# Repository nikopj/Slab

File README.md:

# Slab
Senior Lab: R3Cap, 3D RFID Motion Capture

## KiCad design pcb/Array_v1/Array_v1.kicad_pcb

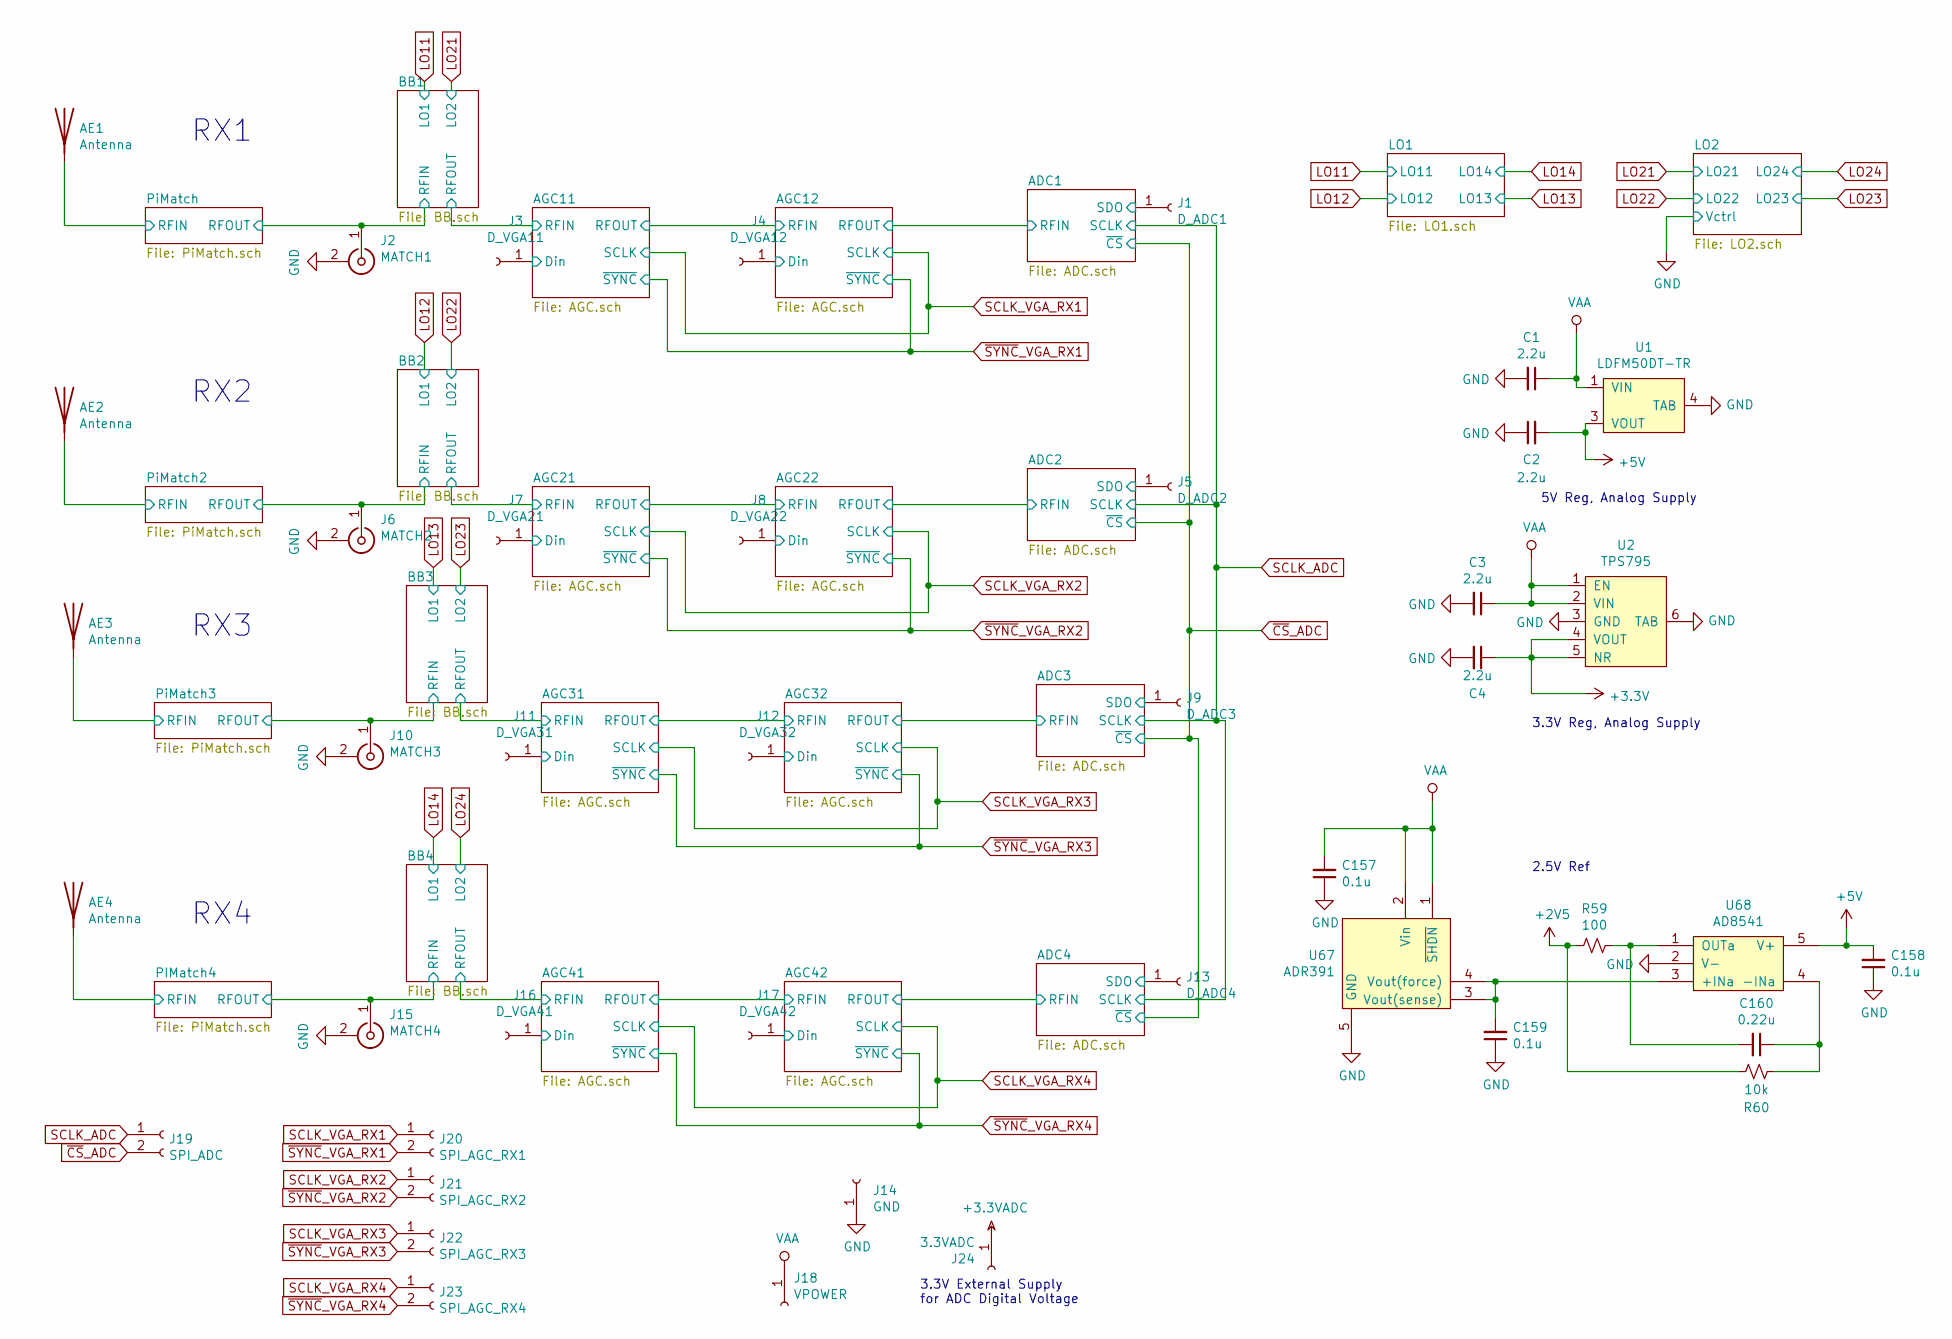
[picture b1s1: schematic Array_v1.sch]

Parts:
AE1, AE2, AE3, AE4: Antenna; 0915AT43A0026
C1, C2, C3, C4: 2.2u; C_0805_2012Metric
C157, C158, C159: 0.1u; C_0603_1608Metric
C160: 0.22u; C_0603_1608Metric
J1: D_ADC1; SolderWirePad_1x01_Drill0.8mm
J2: MATCH1; TE_5-1814832-1
J3: D_VGA11; SolderWirePad_1x01_Drill0.8mm
J4: D_VGA12; SolderWirePad_1x01_Drill0.8mm
J5: D_ADC2; SolderWirePad_1x01_Drill0.8mm
J6: MATCH2; TE_5-1814832-1
J7: D_VGA21; SolderWirePad_1x01_Drill0.8mm
J8: D_VGA22; SolderWirePad_1x01_Drill0.8mm
J9: D_ADC3; SolderWirePad_1x01_Drill0.8mm
J10: MATCH3; TE_5-1814832-1
J11: D_VGA31; SolderWirePad_1x01_Drill0.8mm
J12: D_VGA32; SolderWirePad_1x01_Drill0.8mm
J13: D_ADC4; SolderWirePad_1x01_Drill0.8mm
J14: GND; SolderWirePad_1x01_Drill0.8mm
J15: MATCH4; TE_5-1814832-1
J16: D_VGA41; SolderWirePad_1x01_Drill0.8mm
J17: D_VGA42; SolderWirePad_1x01_Drill0.8mm
J18: VPOWER; SolderWirePad_1x01_Drill0.8mm
J19: SPI_ADC; SolderWirePad_1x02_P3.81mm_Drill0.8mm
J20: SPI_AGC_RX1; SolderWirePad_1x02_P3.81mm_Drill0.8mm
J21: SPI_AGC_RX2; SolderWirePad_1x02_P3.81mm_Drill0.8mm
J22: SPI_AGC_RX3; SolderWirePad_1x02_P3.81mm_Drill0.8mm
J23: SPI_AGC_RX4; SON50P200X200X80-9N
J24: 3.3VADC; SolderWirePad_1x01_Drill0.8mm
R59: 100; C_0603_1608Metric
R60: 10k; C_0603_1608Metric
U1: LDFM50DT-TR; DPAK-TO252
U2: TPS795; SOT127P706X180-6N
U67: ADR391; SOT95P280X100-5N
U68: AD8541; SOT95P290X145-5N

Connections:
+2V5: R59.2, R60.2; also elsewhere on the board
+3.3VADC: J24.1; also elsewhere on the board
+3V3: C4.1, U2.4 (VOUT), U2.5 (NR); also elsewhere on the board
+5V: C2.2, C158.2, U1.3 (VOUT), U68.5 (V+); also elsewhere on the board
/ADC1/SDO: J1.1; also elsewhere on the board
/ADC2/SDO: J5.1; also elsewhere on the board
/ADC3/SDO: J9.1; also elsewhere on the board
/ADC4/SDO: J13.1; also elsewhere on the board
/AGC11/Din: J3.1; also elsewhere on the board
/AGC12/Din: J4.1; also elsewhere on the board
/AGC21/Din: J7.1; also elsewhere on the board
/AGC22/Din: J8.1; also elsewhere on the board
/AGC31/Din: J11.1; also elsewhere on the board
/AGC32/Din: J12.1; also elsewhere on the board
/AGC41/Din: J16.1; also elsewhere on the board
/AGC42/Din: J17.1; also elsewhere on the board
/BB1/RFIN: J2.1 (In); also elsewhere on the board
/BB2/RFIN: J6.1 (In); also elsewhere on the board
/BB3/RFIN: J10.1 (In); also elsewhere on the board
/BB4/RFIN: J15.1 (In); also elsewhere on the board
/PIMatch4/RFIN: AE4.1; also elsewhere on the board
/PiMatch2/RFIN: AE2.1; also elsewhere on the board
/PiMatch3/RFIN: AE3.1; also elsewhere on the board
/PiMatch/RFIN: AE1.1; also elsewhere on the board
GND: C1.2, C2.1, C3.2, C4.2, C157.1, C158.1, C159.1, J2.2 (Ext), J6.2 (Ext), J10.2 (Ext), J14.1, J15.2 (Ext), U1.4 (TAB), U2.3 (GND), U2.6 (TAB), U67.5 (GND), U68.2 (V-); also elsewhere on the board
unnamed: C159.2, U67.3 (Vout(sense)), U67.4 (Vout(force)), U68.3 (+INa)
unnamed: C160.1, R60.1, U68.4 (-INa)
unnamed: C160.2, R59.1, U68.1 (OUTa)
SCLK_ADC: J19.1; also elsewhere on the board
SCLK_VGA_RX1: J20.1; also elsewhere on the board
SCLK_VGA_RX2: J21.1; also elsewhere on the board
SCLK_VGA_RX3: J22.1; also elsewhere on the board
SCLK_VGA_RX4: J23.1; also elsewhere on the board
VAA: C1.1, C3.1, C157.2, J18.1, U1.1 (VIN), U2.1 (EN), U2.2 (VIN), U67.1 (~SHDN), U67.2 (Vin)
~CS~_ADC: J19.2; also elsewhere on the board
~SYNC~_VGA_RX1: J20.2; also elsewhere on the board
~SYNC~_VGA_RX2: J21.2; also elsewhere on the board
~SYNC~_VGA_RX3: J22.2; also elsewhere on the board
~SYNC~_VGA_RX4: J23.2; also elsewhere on the board

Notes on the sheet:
3.3V Reg, Analog Supply
5V Reg, Analog Supply
2.5V Ref
3.3V External Supply for ADC Digital Voltage
RX4
RX3
RX2
RX1

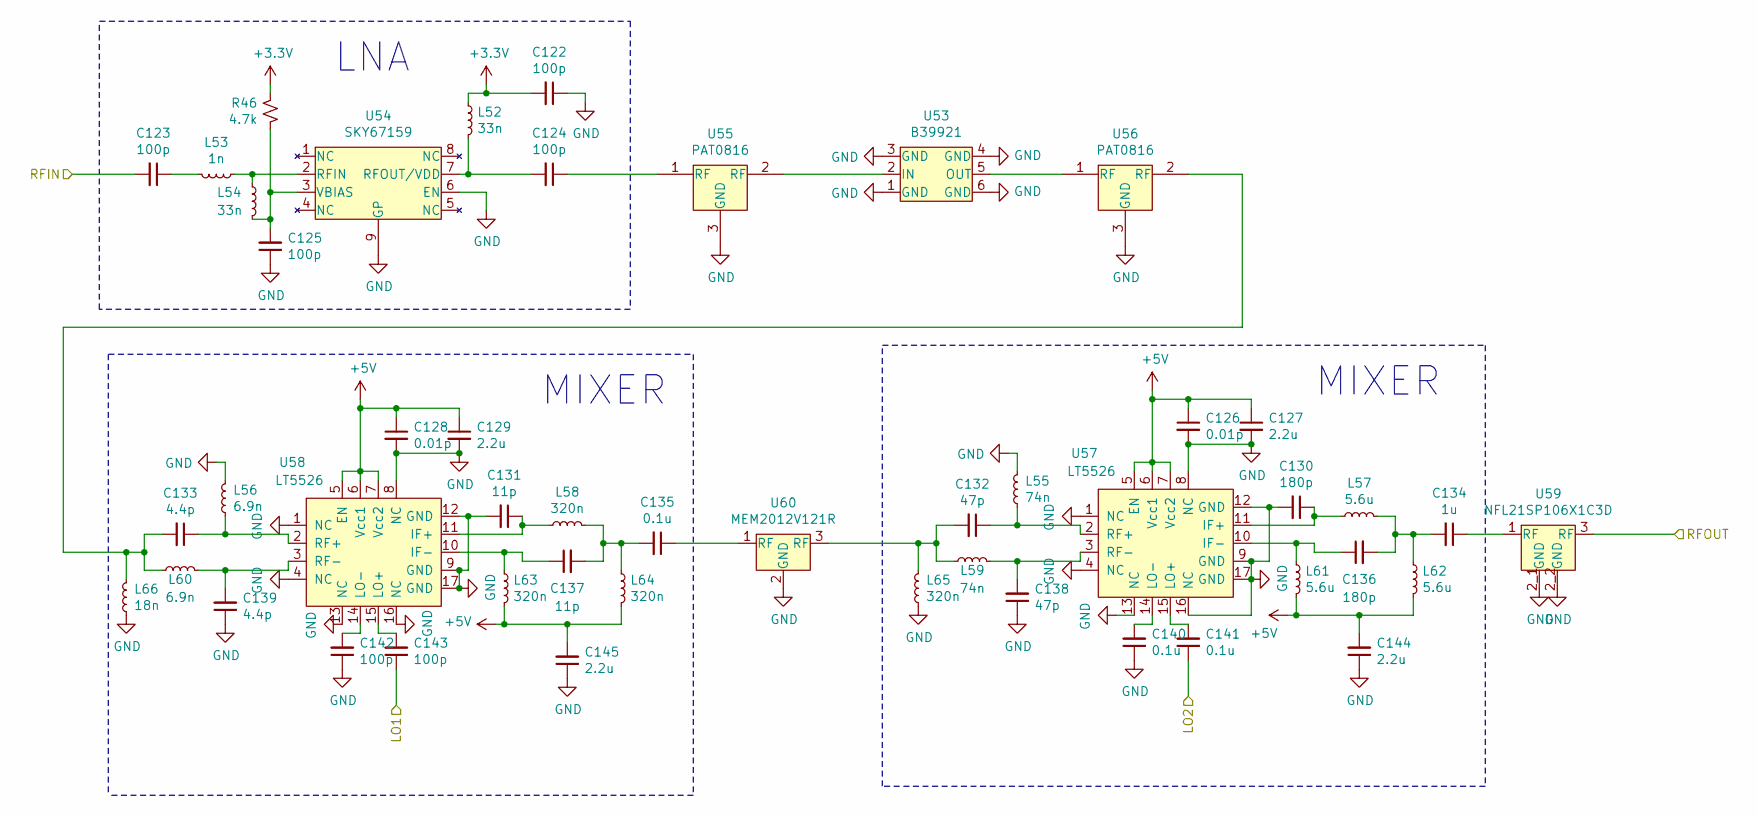
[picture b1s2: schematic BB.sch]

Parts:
C5, C6, C7, C8, C25, C26: 100p; C_0603_1608Metric
C9, C11: 0.01p; C_0603_1608Metric
C10, C12, C27, C28: 2.2u; C_0805_2012Metric
C13, C19: 180p; C_0603_1608Metric
C14, C20: 11p; C_0603_1608Metric
C15, C21: 47p; C_0603_1608Metric
C16, C22: 4.4p; C_0603_1608Metric
C17: 1u; C_0603_1608Metric
C18, C23, C24: 0.1u; C_0603_1608Metric
L1, L3: 33n; C_0603_1608Metric
L2: 1n; C_0603_1608Metric
L4, L8: 74n; C_0603_1608Metric
L5, L9: 6.9n; C_0603_1608Metric
L6, L10, L11: 5.6u; C_0603_1608Metric
L7, L12, L13, L14: 320n; C_0603_1608Metric
L15: 18n; C_0603_1608Metric
R1: 4.7k; C_0603_1608Metric
U3: B39921; SON120P300X300X110-6N
U4: SKY67159; SON50P200X200X80-9N
U5, U6: PAT0816; PAT1220
U7, U8: LT5526; QFN65P400X400X100-17N
U9: NFL21SP106X1C3D; FIL_NFM21PC105B1C3D
U10: MEM2012V121R; FIL_MEM2012V121RT001

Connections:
+3V3: C5.2, L1.1, R1.2; also elsewhere on the board
+5V: C9.1, C10.1, C11.1, C12.1, C27.2, C28.2, L10.2, L11.2, L12.2, L13.2, U7.5 (EN), U7.6 (Vcc1), U7.7 (Vcc2), U8.5 (EN), U8.6 (Vcc1), U8.7 (Vcc2); also elsewhere on the board
/AGC11/RFIN: U9.3 (RF); also elsewhere on the board
/BB1/RFIN: C6.2; also elsewhere on the board
GND: C5.1, C8.1, C9.2, C10.2, C11.2, C12.2, C13.2, C14.2, C21.1, C22.1, C23.1, C25.1, C27.1, C28.1, L4.2, L5.2, L14.1, L15.1, U3.1 (GND), U3.3 (GND), U3.4 (GND), U3.6 (GND), U4.6 (EN), U4.9 (GP), U5.3 (GND), U6.3 (GND), U7.1 (NC), U7.4 (NC), U7.8 (NC), U7.9 (GND), U7.12 (GND), U7.13 (NC), U7.16 (NC), U7.17 (GND), U8.1 (NC), U8.4 (NC), U8.8 (NC), U8.9 (GND), U8.12 (GND), U8.13 (NC), U8.16 (NC), U8.17 (GND), U9.2_1 (GND), U9.2_2 (GND), U9.S1, U9.S2, U9.S3, U10.2 (GND); also elsewhere on the board
LO11: C26.1; also elsewhere on the board
LO21: C24.1; also elsewhere on the board
unnamed: C6.1, L2.2
unnamed: C7.1, U5.1 (RF)
unnamed: C7.2, L1.2, U4.7 (RFOUT/VDD)
unnamed: C8.2, L3.2, R1.1, U4.3 (VBIAS)
unnamed: C13.1, L6.1, U7.11 (IF+)
unnamed: C14.1, L7.1, U8.11 (IF+)
unnamed: C15.1, L4.1, U7.2 (RF+)
unnamed: C15.2, L8.1, L14.2, U10.3 (RF)
unnamed: C16.1, L5.1, U8.2 (RF+)
unnamed: C16.2, L9.1, L15.2, U6.2 (RF)
unnamed: C17.1, U9.1 (RF)
unnamed: C17.2, C19.2, L6.2, L11.1
unnamed: C18.1, U10.1 (RF)
unnamed: C18.2, C20.2, L7.2, L13.1
unnamed: C19.1, L10.1, U7.10 (IF-)
unnamed: C20.1, L12.1, U8.10 (IF-)
unnamed: C21.2, L8.2, U7.3 (RF-)
unnamed: C22.2, L9.2, U8.3 (RF-)
unnamed: C23.2, U7.14 (LO-)
unnamed: C24.2, U7.15 (LO+)
unnamed: C25.2, U8.14 (LO-)
unnamed: C26.2, U8.15 (LO+)
unnamed: L2.1, L3.1, U4.2 (RFIN)
unnamed: U3.2 (IN), U5.2 (RF)
unnamed: U3.5 (OUT), U6.1 (RF)

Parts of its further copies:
C52, C53, C54, C55, C72, C73, C87, C88, C89, C90, C107, C108, C122, C123, C124, C125, C142, C143: 100p; C_0603_1608Metric
C56, C58, C91, C93, C126, C128: 0.01p; C_0603_1608Metric
C57, C59, C74, C75, C92, C94, C109, C110, C127, C129, C144, C145: 2.2u; C_0805_2012Metric
C60, C66, C95, C101, C130, C136: 180p; C_0603_1608Metric
C61, C67, C96, C102, C131, C137: 11p; C_0603_1608Metric
C62, C68, C97, C103, C132, C138: 47p; C_0603_1608Metric
C63, C69, C98, C104, C133, C139: 4.4p; C_0603_1608Metric
C64, C99, C134: 1u; C_0603_1608Metric
C65, C70, C71, C100, C105, C106, C135, C140, C141: 0.1u; C_0603_1608Metric
L18, L20, L35, L37, L52, L54: 33n; C_0603_1608Metric
L19, L36, L53: 1n; C_0603_1608Metric
L21, L25, L38, L42, L55, L59: 74n; C_0603_1608Metric
L22, L26, L39, L43, L56, L60: 6.9n; C_0603_1608Metric
L23, L27, L28, L40, L44, L45, L57, L61, L62: 5.6u; C_0603_1608Metric
L24, L29, L30, L31, L41, L46, L47, L48, L58, L63, L64, L65: 320n; C_0603_1608Metric
L32, L49, L66: 18n; C_0603_1608Metric
R20, R33, R46: 4.7k; C_0603_1608Metric
U25, U39, U53: B39921; SON120P300X300X110-6N
U26, U40, U54: SKY67159; SON50P200X200X80-9N
U27, U28, U41, U42, U55, U56: PAT0816; PAT1220
U29, U30, U43, U44, U57, U58: LT5526; QFN65P400X400X100-17N
U31, U45, U59: NFL21SP106X1C3D; FIL_NFM21PC105B1C3D
U32, U46, U60: MEM2012V121R; FIL_MEM2012V121RT001

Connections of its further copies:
+3V3: C52.2, C87.2, C122.2, L18.1, L35.1, L52.1, R20.2, R33.2, R46.2; also elsewhere on the board
+5V: C56.1, C57.1, C58.1, C59.1, C74.2, C75.2, C91.1, C92.1, C93.1, C94.1, C109.2, C110.2, C126.1, C127.1, C128.1, C129.1, C144.2, C145.2, L27.2, L28.2, L29.2, L30.2, L44.2, L45.2, L46.2, L47.2, L61.2, L62.2, L63.2, L64.2, U29.5 (EN), U29.6 (Vcc1), U29.7 (Vcc2), U30.5 (EN), U30.6 (Vcc1), U30.7 (Vcc2), U43.5 (EN), U43.6 (Vcc1), U43.7 (Vcc2), U44.5 (EN), U44.6 (Vcc1), U44.7 (Vcc2), U57.5 (EN), U57.6 (Vcc1), U57.7 (Vcc2), U58.5 (EN), U58.6 (Vcc1), U58.7 (Vcc2); also elsewhere on the board
/AGC21/RFIN: U31.3 (RF); also elsewhere on the board
/AGC31/RFIN: U45.3 (RF); also elsewhere on the board
/AGC41/RFIN: U59.3 (RF); also elsewhere on the board
/BB2/RFIN: C53.2; also elsewhere on the board
/BB3/RFIN: C88.2; also elsewhere on the board
/BB4/RFIN: C123.2; also elsewhere on the board
GND: C52.1, C55.1, C56.2, C57.2, C58.2, C59.2, C60.2, C61.2, C68.1, C69.1, C70.1, C72.1, C74.1, C75.1, C87.1, C90.1, C91.2, C92.2, C93.2, C94.2, C95.2, C96.2, C103.1, C104.1, C105.1, C107.1, C109.1, C110.1, C122.1, C125.1, C126.2, C127.2, C128.2, C129.2, C130.2, C131.2, C138.1, C139.1, C140.1, C142.1, C144.1, C145.1, L21.2, L22.2, L31.1, L32.1, L38.2, L39.2, L48.1, L49.1, L55.2, L56.2, L65.1, L66.1, U25.1 (GND), U25.3 (GND), U25.4 (GND), U25.6 (GND), U26.6 (EN), U26.9 (GP), U27.3 (GND), U28.3 (GND), U29.1 (NC), U29.4 (NC), U29.8 (NC), U29.9 (GND), U29.12 (GND), U29.13 (NC), U29.16 (NC), U29.17 (GND), U30.1 (NC), U30.4 (NC), U30.8 (NC), U30.9 (GND), U30.12 (GND), U30.13 (NC), U30.16 (NC), U30.17 (GND), U31.2_1 (GND), U31.2_2 (GND), U31.S1, U31.S2, U31.S3, U32.2 (GND), U39.1 (GND), U39.3 (GND), U39.4 (GND), U39.6 (GND), U40.6 (EN), U40.9 (GP), U41.3 (GND), U42.3 (GND), U43.1 (NC), U43.4 (NC), U43.8 (NC), U43.9 (GND), U43.12 (GND), U43.13 (NC), U43.16 (NC), U43.17 (GND), U44.1 (NC), U44.4 (NC), U44.8 (NC), U44.9 (GND), U44.12 (GND), U44.13 (NC), U44.16 (NC), U44.17 (GND), U45.2_1 (GND), U45.2_2 (GND), U45.S1, U45.S2, U45.S3, U46.2 (GND), U53.1 (GND), U53.3 (GND), U53.4 (GND), U53.6 (GND), U54.6 (EN), U54.9 (GP), U55.3 (GND), U56.3 (GND), U57.1 (NC), U57.4 (NC), U57.8 (NC), U57.9 (GND), U57.12 (GND), U57.13 (NC), U57.16 (NC), U57.17 (GND), U58.1 (NC), U58.4 (NC), U58.8 (NC), U58.9 (GND), U58.12 (GND), U58.13 (NC), U58.16 (NC), U58.17 (GND), U59.2_1 (GND), U59.2_2 (GND), U59.S1, U59.S2, U59.S3, U60.2 (GND); also elsewhere on the board
LO12: C73.1; also elsewhere on the board
LO13: C108.1; also elsewhere on the board
LO14: C143.1; also elsewhere on the board
LO22: C71.1; also elsewhere on the board
LO23: C106.1; also elsewhere on the board
LO24: C141.1; also elsewhere on the board
unnamed: C53.1, L19.2
unnamed: C54.1, U27.1 (RF)
unnamed: C54.2, L18.2, U26.7 (RFOUT/VDD)
unnamed: C55.2, L20.2, R20.1, U26.3 (VBIAS)
unnamed: C60.1, L23.1, U29.11 (IF+)
unnamed: C61.1, L24.1, U30.11 (IF+)
unnamed: C62.1, L21.1, U29.2 (RF+)
unnamed: C62.2, L25.1, L31.2, U32.3 (RF)
unnamed: C63.1, L22.1, U30.2 (RF+)
unnamed: C63.2, L26.1, L32.2, U28.2 (RF)
unnamed: C64.1, U31.1 (RF)
unnamed: C64.2, C66.2, L23.2, L28.1
unnamed: C65.1, U32.1 (RF)
unnamed: C65.2, C67.2, L24.2, L30.1
unnamed: C66.1, L27.1, U29.10 (IF-)
unnamed: C67.1, L29.1, U30.10 (IF-)
unnamed: C68.2, L25.2, U29.3 (RF-)
unnamed: C69.2, L26.2, U30.3 (RF-)
unnamed: C70.2, U29.14 (LO-)
unnamed: C71.2, U29.15 (LO+)
unnamed: C72.2, U30.14 (LO-)
unnamed: C73.2, U30.15 (LO+)
unnamed: C88.1, L36.2
unnamed: C89.1, U41.1 (RF)
unnamed: C89.2, L35.2, U40.7 (RFOUT/VDD)
unnamed: C90.2, L37.2, R33.1, U40.3 (VBIAS)
unnamed: C95.1, L40.1, U43.11 (IF+)
unnamed: C96.1, L41.1, U44.11 (IF+)
unnamed: C97.1, L38.1, U43.2 (RF+)
unnamed: C97.2, L42.1, L48.2, U46.3 (RF)
unnamed: C98.1, L39.1, U44.2 (RF+)
unnamed: C98.2, L43.1, L49.2, U42.2 (RF)
unnamed: C99.1, U45.1 (RF)
unnamed: C100.1, U46.1 (RF)
unnamed: C100.2, C102.2, L41.2, L47.1
unnamed: C101.1, L44.1, U43.10 (IF-)
unnamed: C99.2, C101.2, L40.2, L45.1
unnamed: C102.1, L46.1, U44.10 (IF-)
unnamed: C103.2, L42.2, U43.3 (RF-)
unnamed: C104.2, L43.2, U44.3 (RF-)
unnamed: C105.2, U43.14 (LO-)
unnamed: C106.2, U43.15 (LO+)
unnamed: C107.2, U44.14 (LO-)
unnamed: C108.2, U44.15 (LO+)
unnamed: C123.1, L53.2
unnamed: C124.1, U55.1 (RF)
unnamed: C124.2, L52.2, U54.7 (RFOUT/VDD)
unnamed: C125.2, L54.2, R46.1, U54.3 (VBIAS)
unnamed: C130.1, L57.1, U57.11 (IF+)
unnamed: C131.1, L58.1, U58.11 (IF+)
unnamed: C132.1, L55.1, U57.2 (RF+)
unnamed: C132.2, L59.1, L65.2, U60.3 (RF)
unnamed: C133.1, L56.1, U58.2 (RF+)
unnamed: C133.2, L60.1, L66.2, U56.2 (RF)
unnamed: C134.1, U59.1 (RF)
unnamed: C134.2, C136.2, L57.2, L62.1
unnamed: C135.1, U60.1 (RF)
unnamed: C135.2, C137.2, L58.2, L64.1
unnamed: C136.1, L61.1, U57.10 (IF-)
unnamed: C137.1, L63.1, U58.10 (IF-)
unnamed: C138.2, L59.2, U57.3 (RF-)
unnamed: C139.2, L60.2, U58.3 (RF-)
unnamed: C140.2, U57.14 (LO-)
unnamed: C141.2, U57.15 (LO+)
unnamed: C142.2, U58.14 (LO-)
unnamed: C143.2, U58.15 (LO+)
unnamed: L19.1, L20.1, U26.2 (RFIN)
unnamed: L36.1, L37.1, U40.2 (RFIN)
unnamed: L53.1, L54.1, U54.2 (RFIN)
unnamed: U25.2 (IN), U27.2 (RF)
unnamed: U25.5 (OUT), U28.1 (RF)
unnamed: U39.2 (IN), U41.2 (RF)
unnamed: U39.5 (OUT), U42.1 (RF)
unnamed: U53.2 (IN), U55.2 (RF)
unnamed: U53.5 (OUT), U56.1 (RF)

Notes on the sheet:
MIXER
LNA

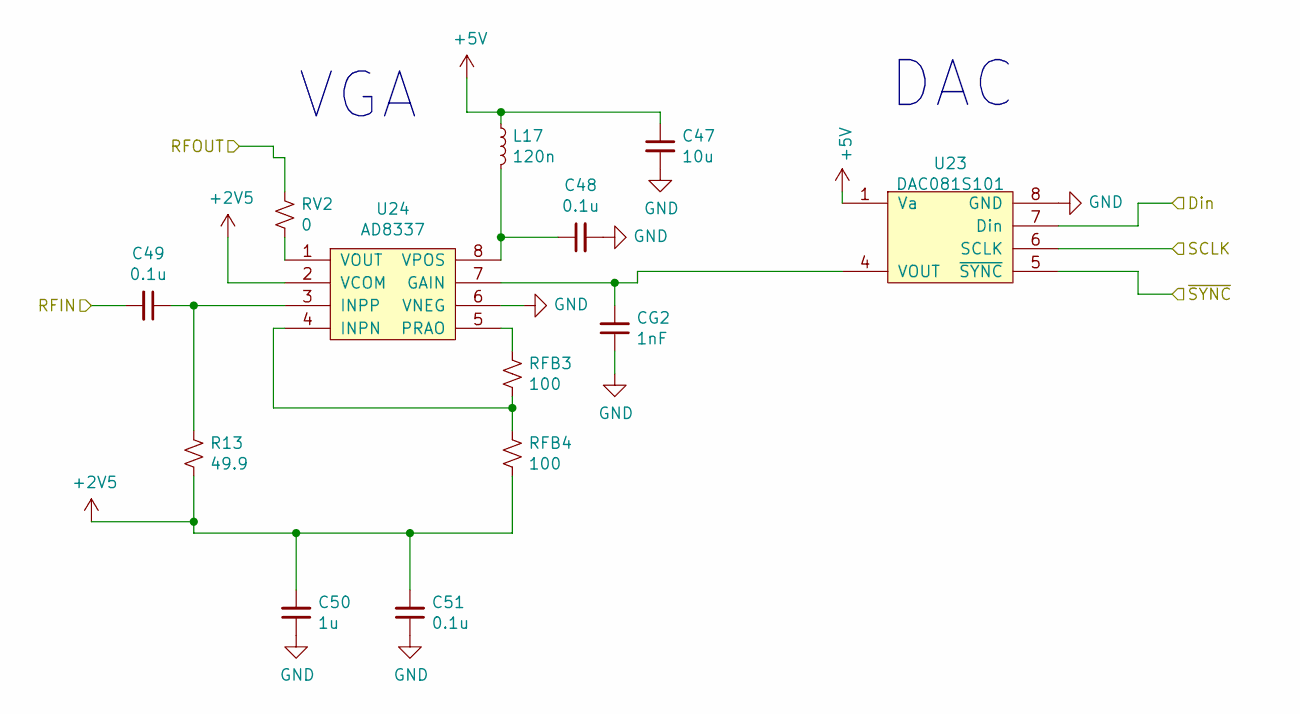
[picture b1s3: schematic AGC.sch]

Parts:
C29: 10u; C_0603_1608Metric
C30, C31, C33: 0.1u; C_0603_1608Metric
C32: 1u; C_0603_1608Metric
CG1: 1nF; C_0603_1608Metric
L16: 120n; C_0603_1608Metric
R2: 49.9; C_0603_1608Metric
RFB1, RFB2: 100; C_0603_1608Metric
RV1: 0; C_0603_1608Metric
U11: DAC081S101; SOP65P490X109-8N
U12: AD8337

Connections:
+2V5: C32.2, C33.2, R2.2, RFB2.2, U12.2 (VCOM); also elsewhere on the board
+5V: C29.1, L16.1, U11.1 (Va); also elsewhere on the board
/AGC11/Din: U11.7 (Din); also elsewhere on the board
/AGC11/RFIN: C31.2; also elsewhere on the board
/AGC12/RFIN: RV1.2; also elsewhere on the board
GND: C29.2, C30.2, C32.1, C33.1, CG1.1, U11.8 (GND), U12.6 (VNEG); also elsewhere on the board
unnamed: C30.1, L16.2, U12.8 (VPOS)
unnamed: C31.1, R2.1, U12.3 (INPP)
unnamed: CG1.2, U11.4 (VOUT), U12.7 (GAIN)
unnamed: RFB1.1, RFB2.1, U12.4 (INPN)
unnamed: RFB1.2, U12.5 (PRAO)
unnamed: RV1.1, U12.1 (VOUT)
SCLK_VGA_RX1: U11.6 (SCLK); also elsewhere on the board
~SYNC~_VGA_RX1: U11.5 (~SYNC); also elsewhere on the board

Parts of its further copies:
C47, C76, C82, C111, C117, C146, C152: 10u; C_0603_1608Metric
C48, C49, C51, C77, C78, C80, C83, C84, C86, C112, C113, C115, C118, C119, C121, C147, C148, C150, C153, C154, C156: 0.1u; C_0603_1608Metric
C50, C79, C85, C114, C120, C149, C155: 1u; C_0603_1608Metric
CG2, CG3, CG4, CG5, CG6, CG7, CG8: 1nF; C_0603_1608Metric
L17, L33, L34, L50, L51, L67, L68: 120n; C_0603_1608Metric
R13, R21, R26, R34, R39, R47, R52: 49.9; C_0603_1608Metric
RFB3, RFB4, RFB5, RFB6, RFB7, RFB8, RFB9, RFB10, RFB11, RFB12, RFB13, RFB14, RFB15, RFB16: 100; C_0603_1608Metric
RV2, RV3, RV4, RV5, RV6, RV7, RV8: 0; C_0603_1608Metric
U23, U33, U37, U47, U51, U61, U65: DAC081S101; SOP65P490X109-8N
U24, U34, U38, U48, U52, U62, U66: AD8337

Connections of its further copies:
+2V5: C50.2, C51.2, C79.2, C80.2, C85.2, C86.2, C114.2, C115.2, C120.2, C121.2, C149.2, C150.2, C155.2, C156.2, R13.2, R21.2, R26.2, R34.2, R39.2, R47.2, R52.2, RFB4.2, RFB6.2, RFB8.2, RFB10.2, RFB12.2, RFB14.2, RFB16.2, U24.2 (VCOM), U34.2 (VCOM), U38.2 (VCOM), U48.2 (VCOM), U52.2 (VCOM), U62.2 (VCOM), U66.2 (VCOM); also elsewhere on the board
+5V: C47.1, C82.1, C111.1, C117.1, C146.1, C152.1, L17.1, L33.1, L34.1, L50.1, L51.1, L67.1, L68.1, U23.1 (Va), U33.1 (Va), U37.1 (Va), U47.1 (Va), U51.1 (Va), U61.1 (Va), U65.1 (Va); also elsewhere on the board
/ADC1/RFIN: RV2.2; also elsewhere on the board
/ADC2/RFIN: RV4.2; also elsewhere on the board
/ADC3/RFIN: RV6.2; also elsewhere on the board
/ADC4/RFIN: RV8.2; also elsewhere on the board
/AGC12/Din: U23.7 (Din); also elsewhere on the board
/AGC12/RFIN: C49.2; also elsewhere on the board
/AGC21/Din: U33.7 (Din); also elsewhere on the board
/AGC21/RFIN: C78.2; also elsewhere on the board
/AGC22/Din: U37.7 (Din); also elsewhere on the board
/AGC22/RFIN: C84.2, RV3.2
/AGC31/Din: U47.7 (Din); also elsewhere on the board
/AGC31/RFIN: C113.2; also elsewhere on the board
/AGC32/Din: U51.7 (Din); also elsewhere on the board
/AGC32/RFIN: C119.2, RV5.2
/AGC41/Din: U61.7 (Din); also elsewhere on the board
/AGC41/RFIN: C148.2; also elsewhere on the board
/AGC42/Din: U65.7 (Din); also elsewhere on the board
/AGC42/RFIN: C154.2, RV7.2
GND: C47.2, C48.2, C50.1, C51.1, C77.2, C79.1, C80.1, C82.2, C83.2, C85.1, C86.1, C111.2, C112.2, C114.1, C115.1, C117.2, C118.2, C120.1, C121.1, C146.2, C147.2, C149.1, C150.1, C152.2, C153.2, C155.1, C156.1, CG2.1, CG3.1, CG4.1, CG5.1, CG6.1, CG7.1, CG8.1, U23.8 (GND), U24.6 (VNEG), U33.8 (GND), U34.6 (VNEG), U37.8 (GND), U38.6 (VNEG), U47.8 (GND), U48.6 (VNEG), U51.8 (GND), U52.6 (VNEG), U61.8 (GND), U62.6 (VNEG), U65.8 (GND), U66.6 (VNEG); also elsewhere on the board
unnamed: C48.1, L17.2, U24.8 (VPOS)
unnamed: C49.1, R13.1, U24.3 (INPP)
unnamed: C77.1, L33.2, U34.8 (VPOS)
unnamed: C78.1, R21.1, U34.3 (INPP)
unnamed: C83.1, L34.2, U38.8 (VPOS)
unnamed: C84.1, R26.1, U38.3 (INPP)
unnamed: C112.1, L50.2, U48.8 (VPOS)
unnamed: C113.1, R34.1, U48.3 (INPP)
unnamed: C118.1, L51.2, U52.8 (VPOS)
unnamed: C119.1, R39.1, U52.3 (INPP)
unnamed: C147.1, L67.2, U62.8 (VPOS)
unnamed: C148.1, R47.1, U62.3 (INPP)
unnamed: C153.1, L68.2, U66.8 (VPOS)
unnamed: C154.1, R52.1, U66.3 (INPP)
unnamed: CG2.2, U23.4 (VOUT), U24.7 (GAIN)
unnamed: CG3.2, U33.4 (VOUT), U34.7 (GAIN)
unnamed: CG4.2, U37.4 (VOUT), U38.7 (GAIN)
unnamed: CG5.2, U47.4 (VOUT), U48.7 (GAIN)
unnamed: CG6.2, U51.4 (VOUT), U52.7 (GAIN)
unnamed: CG7.2, U61.4 (VOUT), U62.7 (GAIN)
unnamed: CG8.2, U65.4 (VOUT), U66.7 (GAIN)
unnamed: RFB3.1, RFB4.1, U24.4 (INPN)
unnamed: RFB3.2, U24.5 (PRAO)
unnamed: RFB5.1, RFB6.1, U34.4 (INPN)
unnamed: RFB5.2, U34.5 (PRAO)
unnamed: RFB7.1, RFB8.1, U38.4 (INPN)
unnamed: RFB7.2, U38.5 (PRAO)
unnamed: RFB9.2, U48.5 (PRAO)
unnamed: RFB9.1, RFB10.1, U48.4 (INPN)
unnamed: RFB11.1, RFB12.1, U52.4 (INPN)
unnamed: RFB11.2, U52.5 (PRAO)
unnamed: RFB13.1, RFB14.1, U62.4 (INPN)
unnamed: RFB13.2, U62.5 (PRAO)
unnamed: RFB15.1, RFB16.1, U66.4 (INPN)
unnamed: RFB15.2, U66.5 (PRAO)
unnamed: RV2.1, U24.1 (VOUT)
unnamed: RV3.1, U34.1 (VOUT)
unnamed: RV4.1, U38.1 (VOUT)
unnamed: RV5.1, U48.1 (VOUT)
unnamed: RV6.1, U52.1 (VOUT)
unnamed: RV7.1, U62.1 (VOUT)
unnamed: RV8.1, U66.1 (VOUT)
SCLK_VGA_RX1: U23.6 (SCLK); also elsewhere on the board
SCLK_VGA_RX2: U33.6 (SCLK), U37.6 (SCLK); also elsewhere on the board
SCLK_VGA_RX3: U47.6 (SCLK), U51.6 (SCLK); also elsewhere on the board
SCLK_VGA_RX4: U61.6 (SCLK), U65.6 (SCLK); also elsewhere on the board
~SYNC~_VGA_RX1: U23.5 (~SYNC); also elsewhere on the board
~SYNC~_VGA_RX2: U33.5 (~SYNC), U37.5 (~SYNC); also elsewhere on the board
~SYNC~_VGA_RX3: U47.5 (~SYNC), U51.5 (~SYNC); also elsewhere on the board
~SYNC~_VGA_RX4: U61.5 (~SYNC), U65.5 (~SYNC); also elsewhere on the board

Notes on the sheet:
DAC
VGA

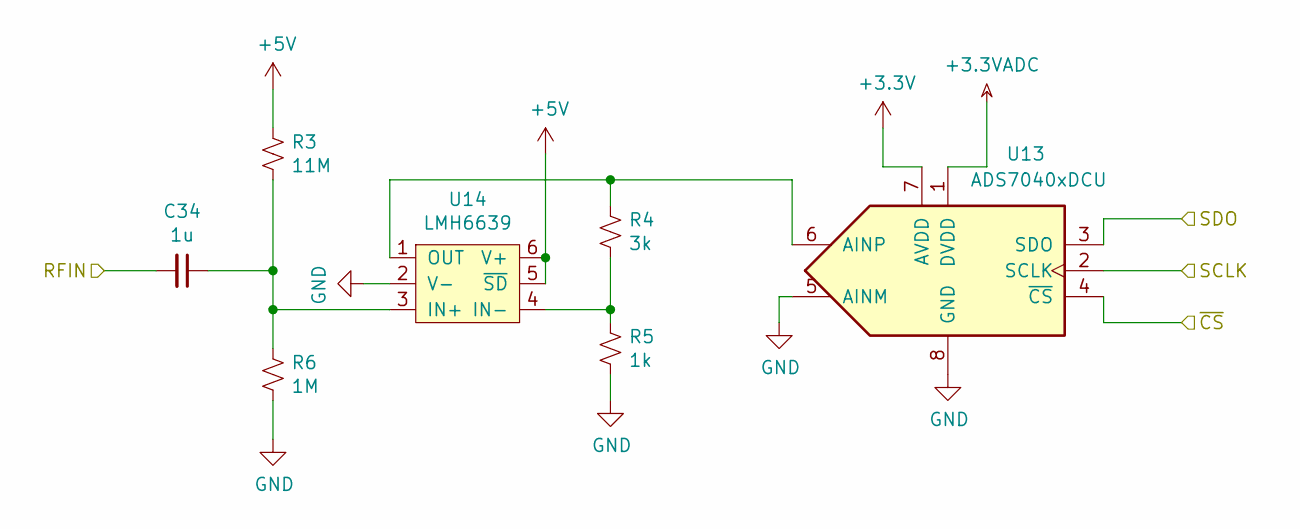
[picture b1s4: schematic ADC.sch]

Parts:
C34: 1u; C_0603_1608Metric
R3: 11M; C_0603_1608Metric
R4: 3k; C_0603_1608Metric
R5: 1k; C_0603_1608Metric
R6: 1M; C_0603_1608Metric
U13: ADS7040xDCU; VSSOP-8_2.3x2mm_P0.5mm
U14: LMH6639; SOT95P284X122-6N

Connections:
+3.3VADC: U13.1 (DVDD); also elsewhere on the board
+3V3: U13.7 (AVDD); also elsewhere on the board
+5V: R3.1, U14.5 (~SD), U14.6 (V+); also elsewhere on the board
/ADC1/RFIN: C34.2; also elsewhere on the board
/ADC1/SDO: U13.3 (SDO); also elsewhere on the board
GND: R5.2, R6.2, U13.5 (AINM), U13.8 (GND), U14.2 (V-); also elsewhere on the board
unnamed: C34.1, R3.2, R6.1, U14.3 (IN+)
unnamed: R4.1, U13.6 (AINP), U14.1 (OUT)
unnamed: R4.2, R5.1, U14.4 (IN-)
SCLK_ADC: U13.2 (SCLK); also elsewhere on the board
~CS~_ADC: U13.4 (~CS); also elsewhere on the board

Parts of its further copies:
C81, C116, C151: 1u; C_0603_1608Metric
R22, R35, R48: 11M; C_0603_1608Metric
R23, R36, R49: 3k; C_0603_1608Metric
R24, R37, R50: 1k; C_0603_1608Metric
R25, R38, R51: 1M; C_0603_1608Metric
U35, U49, U63: ADS7040xDCU; VSSOP-8_2.3x2mm_P0.5mm
U36, U50, U64: LMH6639; SOT95P284X122-6N

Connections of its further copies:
+3.3VADC: U35.1 (DVDD), U49.1 (DVDD), U63.1 (DVDD); also elsewhere on the board
+3V3: U35.7 (AVDD), U49.7 (AVDD), U63.7 (AVDD); also elsewhere on the board
+5V: R22.1, R35.1, R48.1, U36.5 (~SD), U36.6 (V+), U50.5 (~SD), U50.6 (V+), U64.5 (~SD), U64.6 (V+); also elsewhere on the board
/ADC2/RFIN: C81.2; also elsewhere on the board
/ADC2/SDO: U35.3 (SDO); also elsewhere on the board
/ADC3/RFIN: C116.2; also elsewhere on the board
/ADC3/SDO: U49.3 (SDO); also elsewhere on the board
/ADC4/RFIN: C151.2; also elsewhere on the board
/ADC4/SDO: U63.3 (SDO); also elsewhere on the board
GND: R24.2, R25.2, R37.2, R38.2, R50.2, R51.2, U35.5 (AINM), U35.8 (GND), U36.2 (V-), U49.5 (AINM), U49.8 (GND), U50.2 (V-), U63.5 (AINM), U63.8 (GND), U64.2 (V-); also elsewhere on the board
unnamed: C81.1, R22.2, R25.1, U36.3 (IN+)
unnamed: C116.1, R35.2, R38.1, U50.3 (IN+)
unnamed: C151.1, R48.2, R51.1, U64.3 (IN+)
unnamed: R23.1, U35.6 (AINP), U36.1 (OUT)
unnamed: R23.2, R24.1, U36.4 (IN-)
unnamed: R36.1, U49.6 (AINP), U50.1 (OUT)
unnamed: R36.2, R37.1, U50.4 (IN-)
unnamed: R49.1, U63.6 (AINP), U64.1 (OUT)
unnamed: R49.2, R50.1, U64.4 (IN-)
SCLK_ADC: U35.2 (SCLK), U49.2 (SCLK), U63.2 (SCLK); also elsewhere on the board
~CS~_ADC: U35.4 (~CS), U49.4 (~CS), U63.4 (~CS); also elsewhere on the board

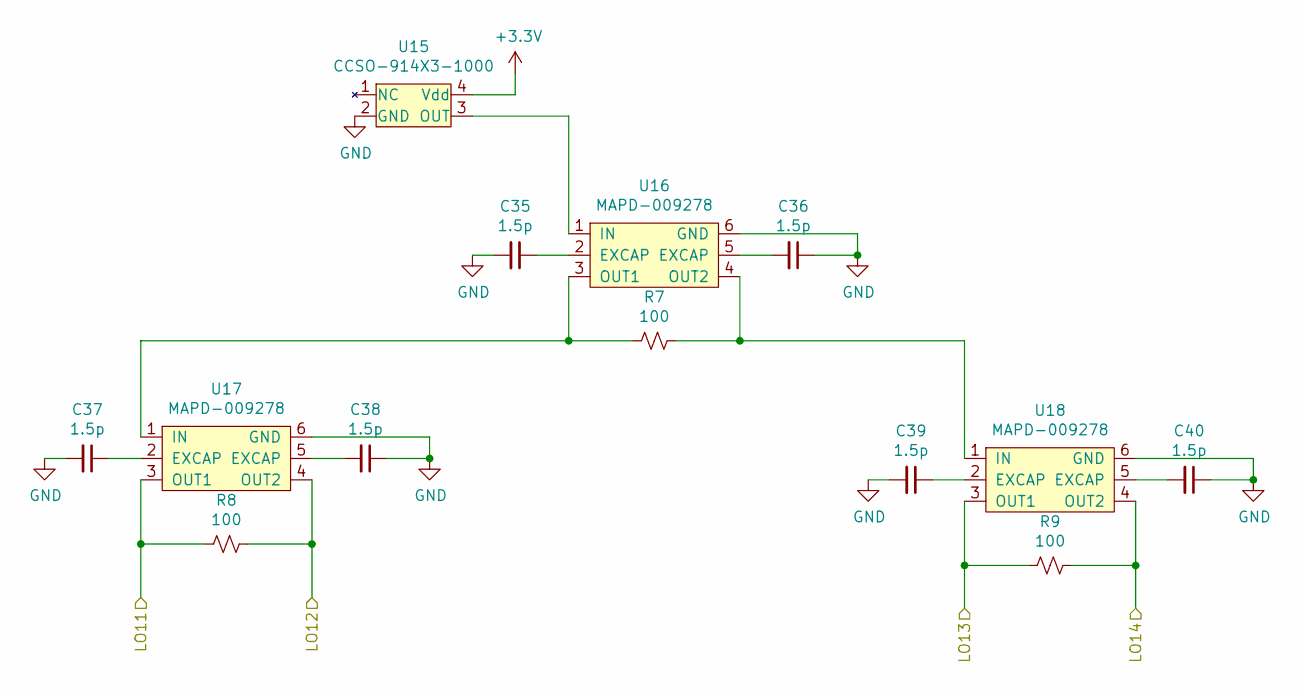
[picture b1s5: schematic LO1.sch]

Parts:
C35, C36, C37, C38, C39, C40: 1.5p; C_0603_1608Metric
R7, R8, R9: 100; C_0603_1608Metric
U15: CCSO-914X3-1000; OSCSC508P1420X914X530-4N
U16, U17, U18: MAPD-009278

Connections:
+3V3: U15.4 (Vdd); also elsewhere on the board
GND: C35.2, C36.1, C37.2, C38.1, C39.2, C40.1, U15.2 (GND), U16.6 (GND), U17.6 (GND), U18.6 (GND); also elsewhere on the board
LO11: R9.2, U18.4 (OUT2); also elsewhere on the board
LO12: R8.2, U17.4 (OUT2); also elsewhere on the board
LO13: R8.1, U17.3 (OUT1); also elsewhere on the board
LO14: R9.1, U18.3 (OUT1); also elsewhere on the board
unnamed: C35.1, U16.2 (EXCAP)
unnamed: C36.2, U16.5 (EXCAP)
unnamed: C37.1, U17.2 (EXCAP)
unnamed: C38.2, U17.5 (EXCAP)
unnamed: C39.1, U18.2 (EXCAP)
unnamed: C40.2, U18.5 (EXCAP)
unnamed: R7.1, U16.3 (OUT1), U17.1 (IN)
unnamed: R7.2, U16.4 (OUT2), U18.1 (IN)
unnamed: U15.3 (OUT), U16.1 (IN)

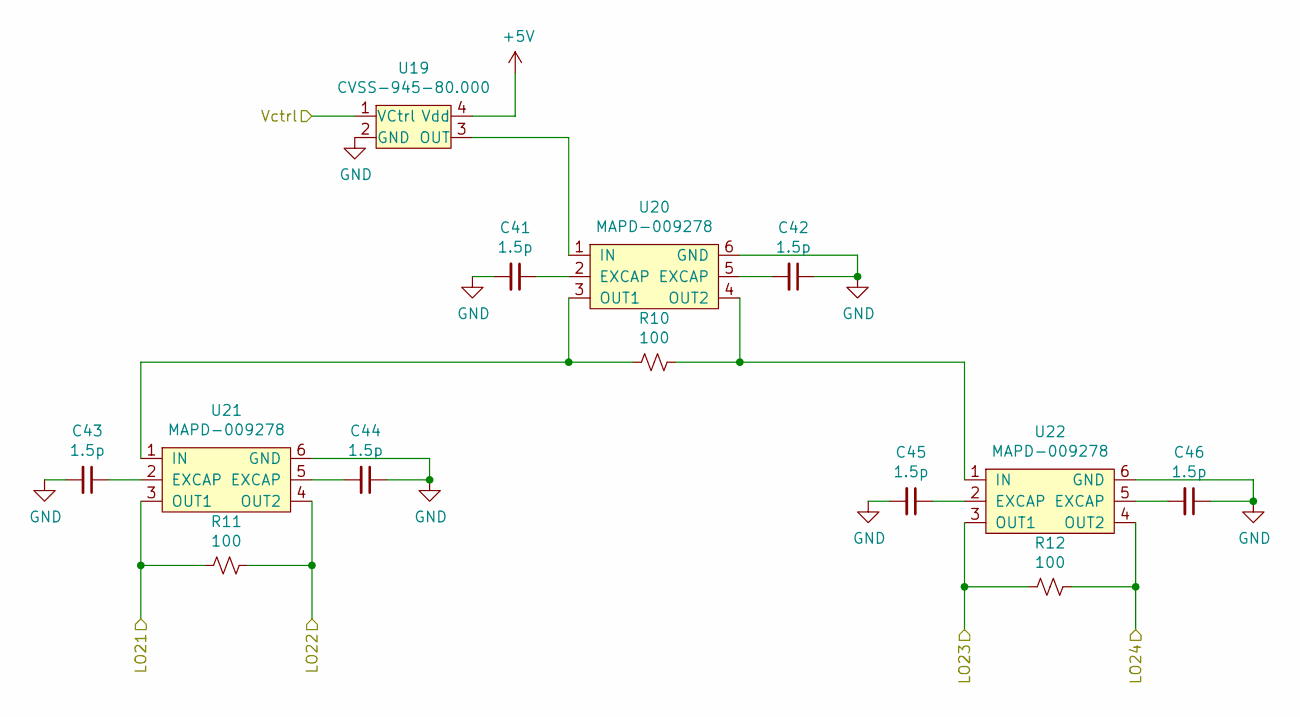
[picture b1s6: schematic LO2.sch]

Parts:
C41, C42, C43, C44, C45, C46: 1.5p; C_0603_1608Metric
R10, R11, R12: 100; C_0603_1608Metric
U19: CVSS-945-80.000; OSCSC508P1420X914X530-4N
U20, U21, U22: MAPD-009278

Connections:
+5V: U19.4 (Vdd); also elsewhere on the board
GND: C41.2, C42.1, C43.2, C44.1, C45.2, C46.1, U19.1 (VCtrl), U19.2 (GND), U20.6 (GND), U21.6 (GND), U22.6 (GND); also elsewhere on the board
LO21: R11.1, U21.3 (OUT1); also elsewhere on the board
LO22: R12.1, U22.3 (OUT1); also elsewhere on the board
LO23: R12.2, U22.4 (OUT2); also elsewhere on the board
LO24: R11.2, U21.4 (OUT2); also elsewhere on the board
unnamed: C41.1, U20.2 (EXCAP)
unnamed: C42.2, U20.5 (EXCAP)
unnamed: C43.1, U21.2 (EXCAP)
unnamed: C44.2, U21.5 (EXCAP)
unnamed: C45.1, U22.2 (EXCAP)
unnamed: C46.2, U22.5 (EXCAP)
unnamed: R10.1, U20.3 (OUT1), U21.1 (IN)
unnamed: R10.2, U20.4 (OUT2), U22.1 (IN)
unnamed: U19.3 (OUT), U20.1 (IN)

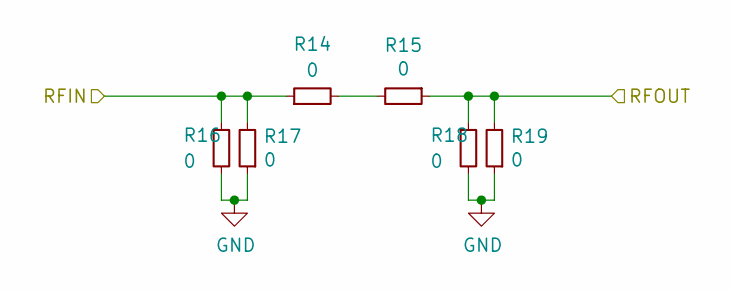
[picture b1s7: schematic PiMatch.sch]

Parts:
R14, R15, R16, R17, R18, R19: 0; C_0402_1005Metric

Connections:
/BB1/RFIN: R15.1, R18.1, R19.2; also elsewhere on the board
/PiMatch/RFIN: R14.1, R16.1, R17.2; also elsewhere on the board
GND: R16.2, R17.1, R18.2, R19.1; also elsewhere on the board
unnamed: R14.2, R15.2

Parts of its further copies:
R27, R28, R29, R30, R31, R32, R40, R41, R42, R43, R44, R45, R53, R54, R55, R56, R57, R58: 0; C_0402_1005Metric

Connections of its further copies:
/BB2/RFIN: R28.1, R31.1, R32.2; also elsewhere on the board
/BB3/RFIN: R41.1, R44.1, R45.2; also elsewhere on the board
/BB4/RFIN: R54.1, R57.1, R58.2; also elsewhere on the board
/PIMatch4/RFIN: R53.1, R55.1, R56.2; also elsewhere on the board
/PiMatch2/RFIN: R27.1, R29.1, R30.2; also elsewhere on the board
/PiMatch3/RFIN: R40.1, R42.1, R43.2; also elsewhere on the board
GND: R29.2, R30.1, R31.2, R32.1, R42.2, R43.1, R44.2, R45.1, R55.2, R56.1, R57.2, R58.1; also elsewhere on the board
unnamed: R27.2, R28.2
unnamed: R40.2, R41.2
unnamed: R53.2, R54.2
